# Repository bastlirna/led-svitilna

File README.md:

# LED svítilna

LED svítilna k propagaci na akcích a tréningu pájeni.

<p align="center">

</p>

## Součástky

* SMD Rezistor R1206 100R
* LED 5MM RED-ORANGE 4200
* Mikrospínač TD-03XG-T SMD
* Držák baterie do DPS pro CR2032 BC2001
* Baterie CR2032
* Fotocuprextit 200x150x1,5 jednovrstvý (pro 20 ks)

## Dokumenty

* [Návod](doc/led_svitilna_navod.pdf) (pdf)
* [DPS](pcb/led_svitilna_16pcs.pdf) (pdf)

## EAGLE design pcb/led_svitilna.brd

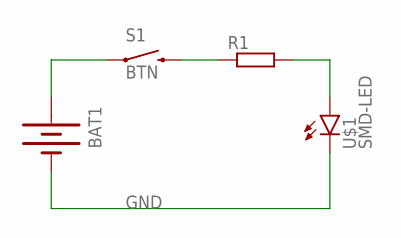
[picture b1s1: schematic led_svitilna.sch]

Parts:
BAT1: BATTERY20SMD; BATTCON_20MM
R1: R-EU_R1206; R1206
S1: BTN; TACTILE_SWITCH_TALL
U$1: SMD-LED

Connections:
GND: BAT1.2 (-), U$1.K (C)
unnamed: BAT1.1 (+), S1.A2 (1)
unnamed: R1.1, S1.B2 (2)
unnamed: R1.2, U$1.A

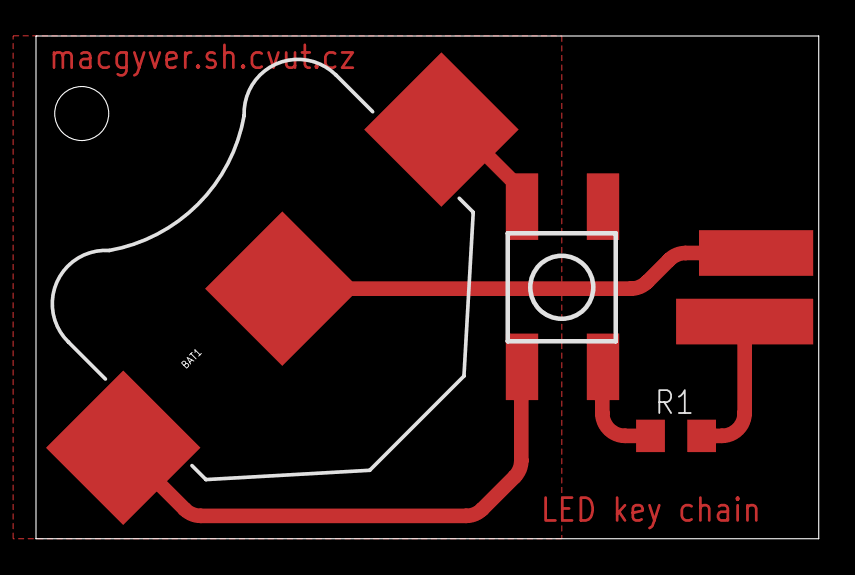
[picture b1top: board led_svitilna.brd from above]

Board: 2 copper layers, 43.5 x 27.9 mm, 4 parts (0 on the bottom side), 4 nets.

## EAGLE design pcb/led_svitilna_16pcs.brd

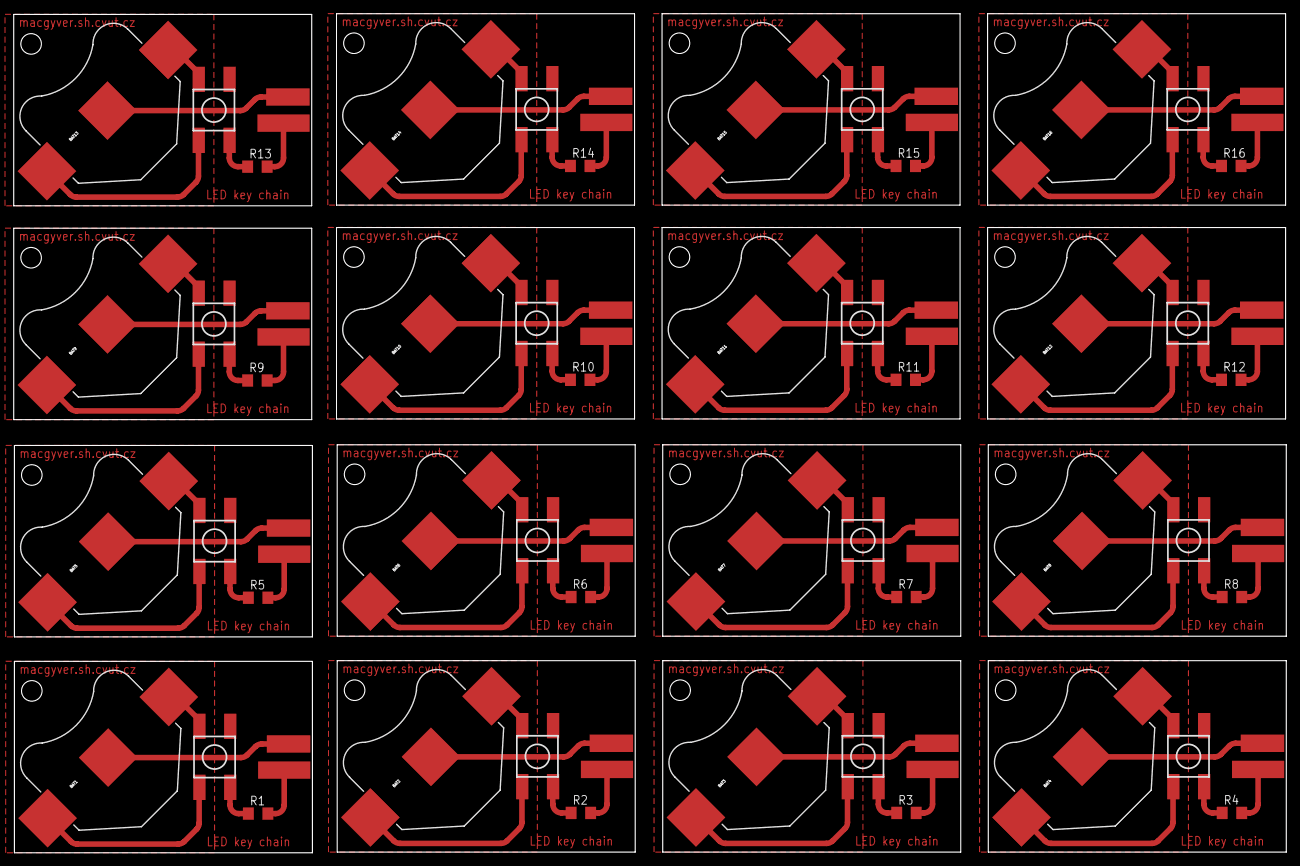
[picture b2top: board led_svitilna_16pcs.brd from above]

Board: 2 copper layers, 185.7 x 122.4 mm, 64 parts (0 on the bottom side), 64 nets.

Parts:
BAT1, BAT2, BAT3, BAT4, BAT5, BAT6, BAT7, BAT8, BAT9, BAT10, BAT11, BAT12, BAT13, BAT14, BAT15, BAT16: BATTCON_20MM
R1, R2, R3, R4, R5, R6, R7, R8, R9, R10, R11, R12, R13, R14, R15, R16: R1206
S1, S2, S3, S4, S5, S6, S7, S8, S9, S10, S11, S12, S13, S14, S15, S16: BTN; TACTILE_SWITCH_TALL
U$1, U$2, U$3, U$4, U$5, U$6, U$7, U$8, U$9, U$10, U$11, U$12, U$13, U$14, U$15, U$16: SMD-LED

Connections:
GND: BAT1.2, U$1.K
GND1: BAT2.2, U$2.K
GND2: BAT3.2, U$3.K
GND3: BAT4.2, U$4.K
GND4: BAT5.2, U$5.K
GND5: BAT6.2, U$6.K
GND6: BAT7.2, U$7.K
GND7: BAT8.2, U$8.K
GND8: BAT9.2, U$9.K
GND9: BAT10.2, U$10.K
GND10: BAT11.2, U$11.K
GND11: BAT12.2, U$12.K
GND12: BAT13.2, U$13.K
GND13: BAT14.2, U$14.K
GND14: BAT15.2, U$15.K
GND15: BAT16.2, U$16.K
unnamed: BAT1.1, S1.A2
unnamed: R1.1, S1.B2
unnamed: R1.2, U$1.A
unnamed: BAT2.1, S2.A2
unnamed: R2.1, S2.B2
unnamed: R2.2, U$2.A
unnamed: BAT3.1, S3.A2
unnamed: R3.1, S3.B2
unnamed: R3.2, U$3.A
unnamed: BAT4.1, S4.A2
unnamed: R4.1, S4.B2
unnamed: R4.2, U$4.A
unnamed: BAT5.1, S5.A2
unnamed: R5.1, S5.B2
unnamed: R5.2, U$5.A
unnamed: BAT6.1, S6.A2
unnamed: R6.1, S6.B2
unnamed: R6.2, U$6.A
unnamed: BAT7.1, S7.A2
unnamed: R7.1, S7.B2
unnamed: R7.2, U$7.A
unnamed: BAT8.1, S8.A2
unnamed: R8.1, S8.B2
unnamed: R8.2, U$8.A
unnamed: BAT9.1, S9.A2
unnamed: R9.1, S9.B2
unnamed: R9.2, U$9.A
unnamed: BAT10.1, S10.A2
unnamed: R10.1, S10.B2
unnamed: R10.2, U$10.A
unnamed: BAT11.1, S11.A2
unnamed: R11.1, S11.B2
unnamed: R11.2, U$11.A
unnamed: BAT12.1, S12.A2
unnamed: R12.1, S12.B2
unnamed: R12.2, U$12.A
unnamed: BAT13.1, S13.A2
unnamed: R13.1, S13.B2
unnamed: R13.2, U$13.A
unnamed: BAT14.1, S14.A2
unnamed: R14.1, S14.B2
unnamed: R14.2, U$14.A
unnamed: BAT15.1, S15.A2
unnamed: R15.1, S15.B2
unnamed: R15.2, U$15.A
unnamed: BAT16.1, S16.A2
unnamed: R16.1, S16.B2
unnamed: R16.2, U$16.A

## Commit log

2017-06-27 Text podklady.
2017-06-27 Eagle - podklady
2017-06-27 readme soucastky
2017-06-29 Rozdělení na doc a pcb
2017-06-29 Podklady pro pcb v návodu
2017-06-29 Ilustrační foto
2017-06-29 Přidáno DPS v pdf formátu pro ilustraci
2017-06-29 Doplněna baterie do seznamu součástek
2017-11-02 base48 logo added

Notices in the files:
parts and their libraries:
SparkFun-Electromechanical: Licensing: Creative Commons ShareAlike 4.0 International - https://creativecommons.org/licenses/by-sa/4.0
